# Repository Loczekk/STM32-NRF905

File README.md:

# STM32-NRF905
Design of NRF905 dongle

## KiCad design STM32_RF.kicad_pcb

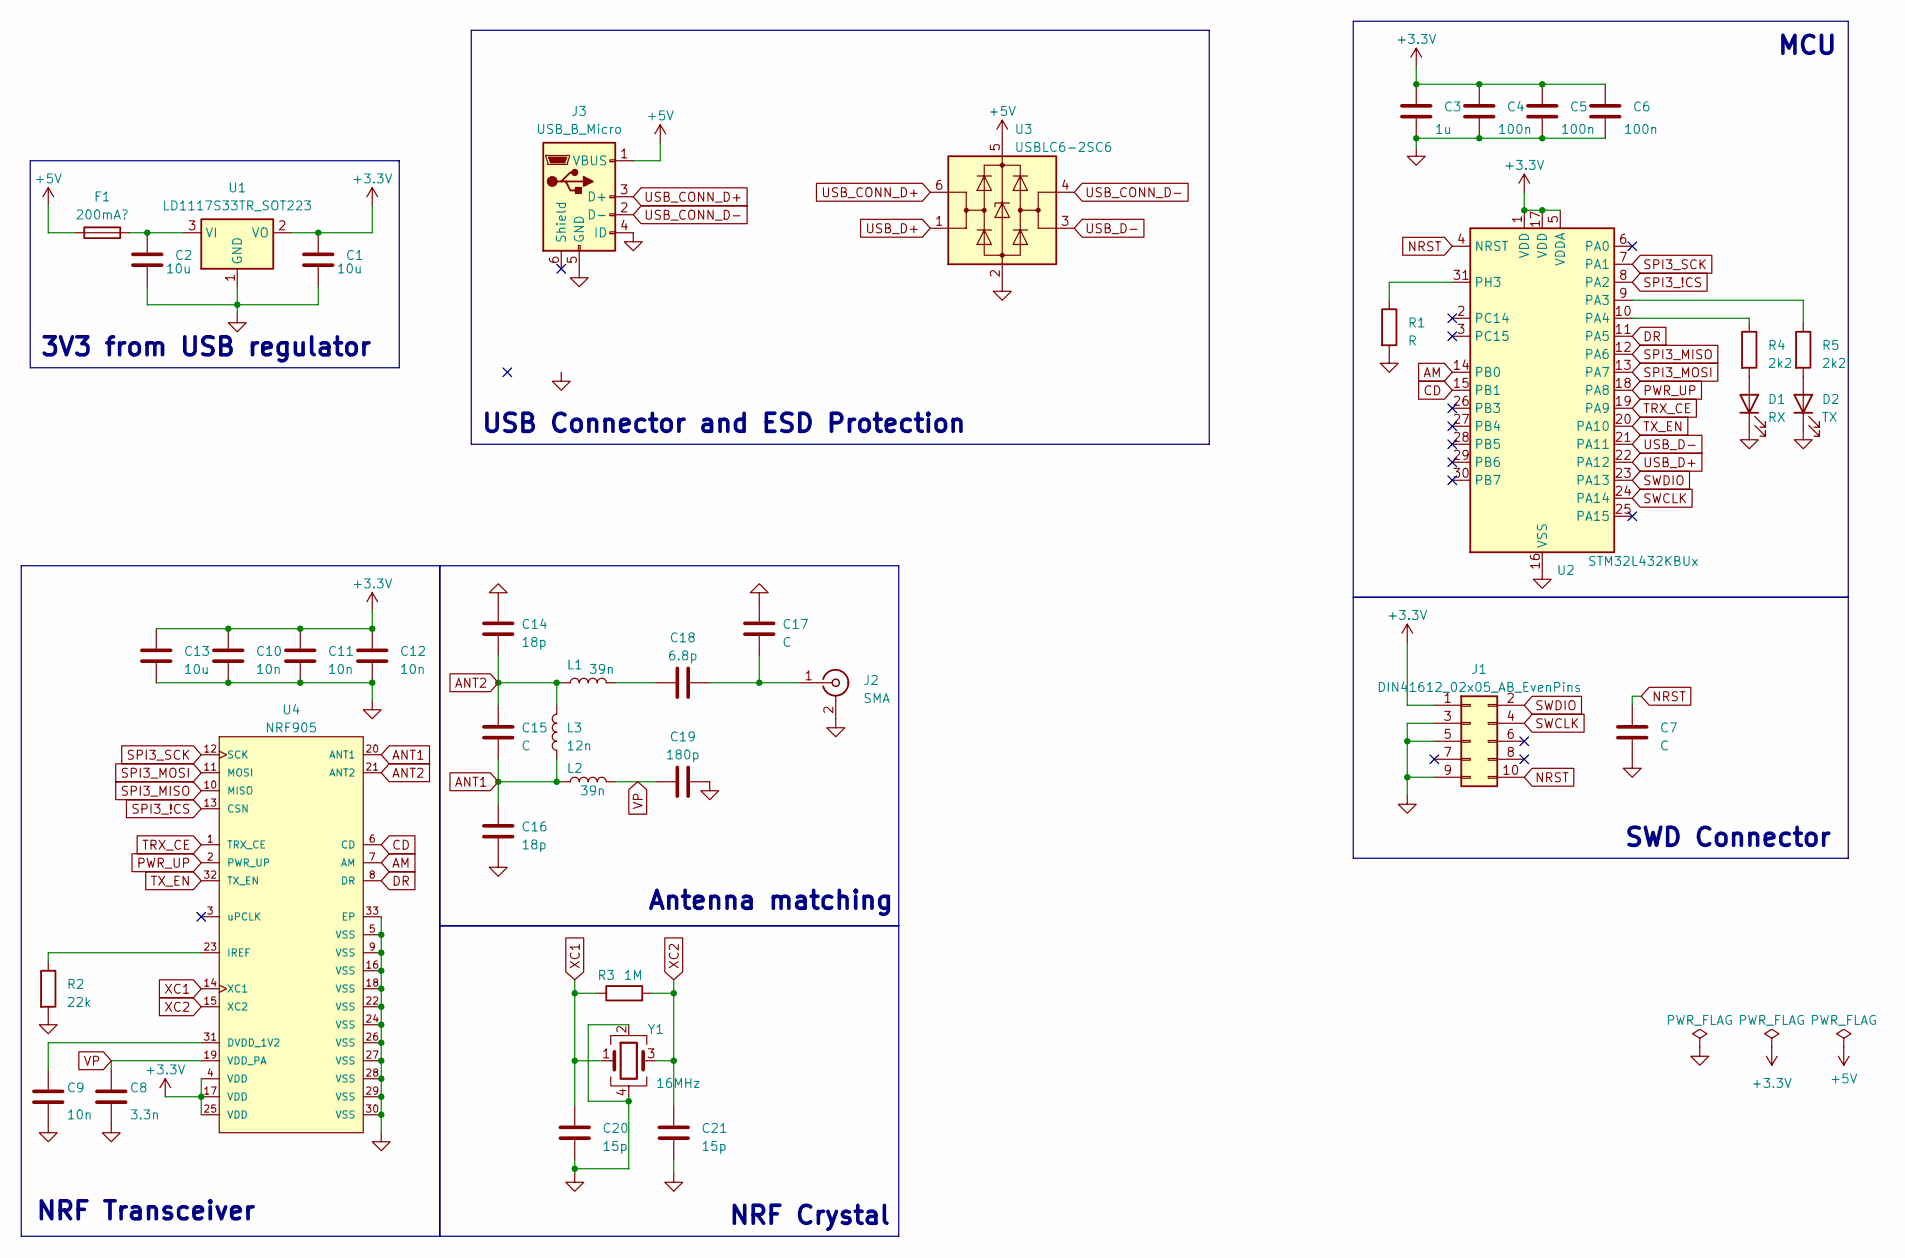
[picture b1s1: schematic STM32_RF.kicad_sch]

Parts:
C1, C2, C13: 10u; C_0805_2012Metric
C3: 1u; C_0805_2012Metric
C4, C5, C6: 100n; C_0603_1608Metric
C7, C15, C17: C; C_0603_1608Metric
C8: 3.3n; C_0603_1608Metric
C9, C10, C11, C12: 10n; C_0603_1608Metric
C14, C16: 18p; C_0603_1608Metric
C18: 6.8p; C_0603_1608Metric
C19: 180p; C_0603_1608Metric
C20, C21: 15p; C_0603_1608Metric
D1: RX; D_0805_2012Metric
D2: TX; D_0805_2012Metric
F1: 200mA?; Fuse_1206_3216Metric
J1: DIN41612_02x05_AB_EvenPins; PinHeader_2x05_P1.27mm_Vertical
J2: SMA; SMA_Amphenol_132289_EdgeMount
J3: USB_B_Micro; USB_Micro-B_Amphenol_10103594-0001LF_Horizontal
L1, L2: 39n; L_0603_1608Metric
L3: 12n; L_0603_1608Metric
R1: R; R_0805_2012Metric
R2: 22k; R_0805_2012Metric
R3: 1M; R_0805_2012Metric
R4, R5: 2k2; R_0805_2012Metric
U1: LD1117S33TR_SOT223; SOT-223-3_TabPin2
U2: STM32L432KBUx; QFN-32-1EP_5x5mm_P0.5mm_EP3.45x3.45mm
U3: USBLC6-2SC6; SOT-23-6_Handsoldering
U4: NRF905; QFN-32-1EP_5x5mm_P0.5mm_EP3.3x3.3mm; Current Rating 10 A; Tolerance 10%
Y1: 16MHz; Crystal_SMD_3225-4Pin_3.2x2.5mm

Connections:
+3.3V: C1.1, C3.1, C4.1, C5.1, C6.1, C10.1, C11.1, C12.1, C13.1, J1.1 (Pin_a2), U1.2 (VO), U2.1 (VDD), U2.5 (VDDA), U2.17 (VDD), U4.4 (VDD), U4.17 (VDD), U4.25 (VDD)
+5V: F1.1, J3.1 (VBUS), U3.5 (VBUS)
AM: U2.14 (PB0), U4.7 (AM)
ANT1: C15.2, C16.1, L2.1, L3.1, U4.20 (ANT1)
ANT2: C14.2, C15.1, L1.1, L3.2, U4.21 (ANT2)
CD: U2.15 (PB1), U4.6 (CD)
DR: U2.11 (PA5), U4.8 (DR)
GND: C1.2, C2.2, C3.2, C4.2, C5.2, C6.2, C7.2, C8.2, C9.2, C10.2, C11.2, C12.2, C13.2, C14.1, C16.2, C17.1, C19.2, C20.2, C21.2, D1.1 (K), D2.1 (K), J1.3 (Pin_a4), J1.5 (Pin_a6), J1.9 (Pin_a10), J2.2 (Ext), J3.4 (ID), J3.5 (GND), R1.2, R2.2, U1.1 (GND), U2.16 (VSS), U2.32 (VSS), U2.33 (VSS), U3.2 (GND), U4.5 (VSS), U4.9 (VSS), U4.16 (VSS), U4.18 (VSS), U4.22 (VSS), U4.24 (VSS), U4.26 (VSS), U4.27 (VSS), U4.28 (VSS), U4.29 (VSS), U4.30 (VSS), U4.33 (EP), Y1.2, Y1.4
NRST: C7.1, J1.10 (Pin_b10), U2.4 (NRST)
unnamed: C18.1, L1.2
unnamed: D1.2 (A), R4.2
unnamed: D2.2 (A), R5.2
unnamed: C17.2, C18.2, J2.1 (In)
unnamed: C2.1, F1.2, U1.3 (VI)
unnamed: R5.1, U2.9 (PA3)
unnamed: R4.1, U2.10 (PA4)
unnamed: R1.1, U2.31 (PH3)
unnamed: C9.1, U4.31 (DVDD_1V2)
unnamed: R2.1, U4.23 (IREF)
PWR_UP: U2.18 (PA8), U4.2 (PWR_UP)
SPI3_!CS: U2.8 (PA2), U4.13 (CSN)
SPI3_MISO: U2.12 (PA6), U4.10 (MISO)
SPI3_MOSI: U2.13 (PA7), U4.11 (MOSI)
SPI3_SCK: U2.7 (PA1), U4.12 (SCK)
SWCLK: J1.4 (Pin_b4), U2.24 (PA14)
SWDIO: J1.2 (Pin_b2), U2.23 (PA13)
TRX_CE: U2.19 (PA9), U4.1 (TRX_CE)
TX_EN: U2.20 (PA10), U4.32 (TX_EN)
USB_CONN_D+: J3.3 (D+), U3.6 (I/O1)
USB_CONN_D-: J3.2 (D-), U3.4 (I/O2)
USB_D+: U2.22 (PA12), U3.1 (I/O1)
USB_D-: U2.21 (PA11), U3.3 (I/O2)
VP: C8.1, C19.1, L2.2, U4.19 (VDD_PA)
XC1: C20.1, R3.1, U4.14 (XC1), Y1.1
XC2: C21.1, R3.2, U4.15 (XC2), Y1.3

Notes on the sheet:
MCU
NRF Transceiver
NRF Crystal
USB Connector and ESD Protection
Antenna matching
3V3 from USB regulator
SWD Connector

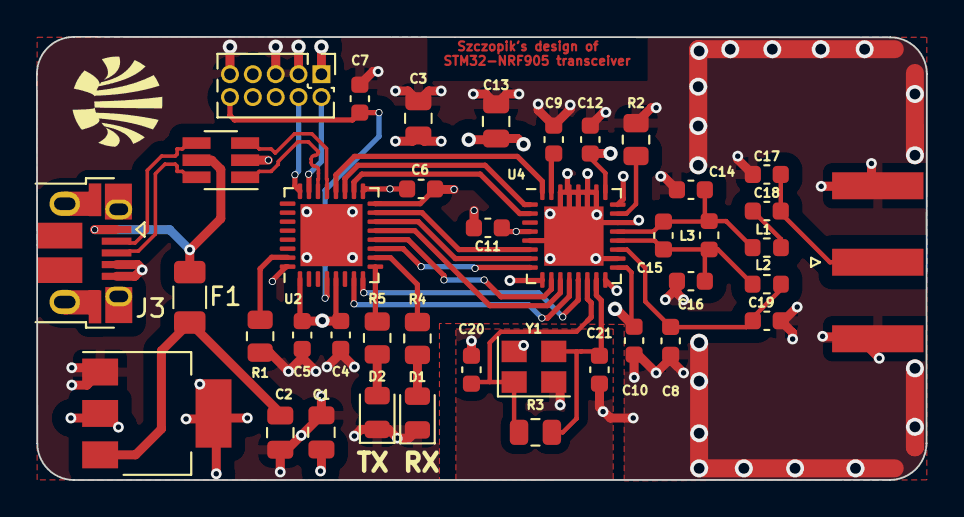
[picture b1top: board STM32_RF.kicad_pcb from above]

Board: 4 copper layers, 49.4 x 24.6 mm, 41 parts (0 on the bottom side), 35 nets.

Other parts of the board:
*: LOGO; logo_sol_malutkie
